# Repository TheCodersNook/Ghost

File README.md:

# Ghost Drive

## Idea
The whole idea is that it allows the cloud drives people pay for to be physical and work with any device so long as the ghost drive is connected to wifi. The ghost drive never holds any data but only allows for the file paths to be seen, new files to be added to cloud via the ghost drive.

<br>
<br>

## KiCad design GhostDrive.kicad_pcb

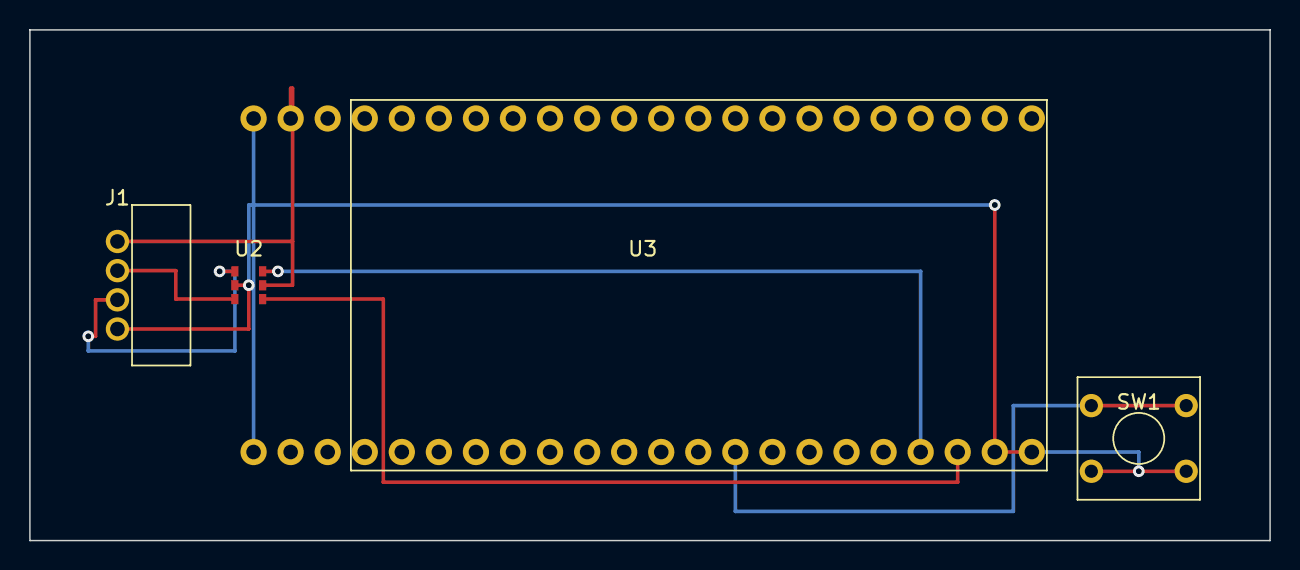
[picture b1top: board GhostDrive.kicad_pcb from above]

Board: 2 copper layers, 85.0 x 35.0 mm, 4 parts (0 on the bottom side), 7 nets.

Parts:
J1: USB-A_Male_DIP_4pin
SW1: SW_Tactile_6x6mm
U2: SOT-23-6
U3: DevKitC-1_2x22

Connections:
BOOT: SW1.1, SW1.2, U3.31
D+: J1.3, U2.3
D+_OUT: U2.4, U3.26
D-: J1.2, U2.1
D-_OUT: U2.6, U3.25
GND: J1.4, SW1.3, SW1.4, U2.2, U3.22, U3.23, U3.24, U3.44
VBUS: J1.1, U2.5, U3.21
